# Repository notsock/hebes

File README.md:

# notcorne
Corne-styled Kailh Choc switch keyboard.

# Features
MCU: ATMega32u4 (Pro Micro)
Switches: Kailh Choc
Connectivity: RJ11 for both halves

# To-do
- Adjust collum stagger
- Adjust thumb cluster

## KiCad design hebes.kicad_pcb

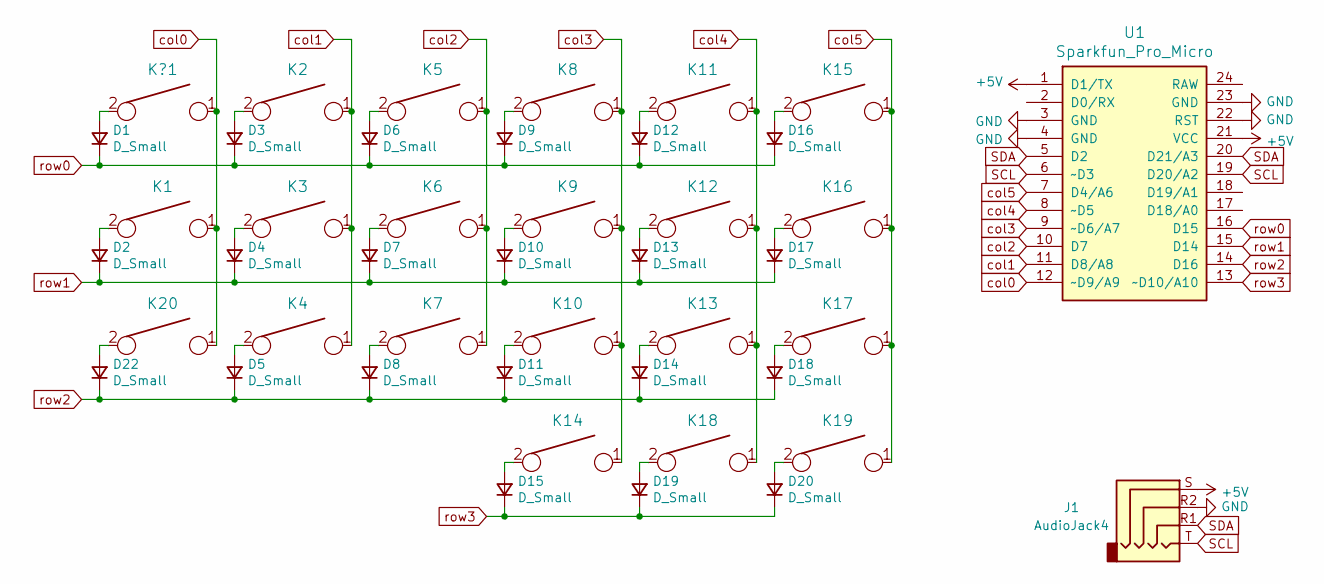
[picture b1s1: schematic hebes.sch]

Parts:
D1, D2, D3, D4, D5, D6, D7, D8, D9, D10, D11, D12, D13, D14, D15, D16, D17, D18, D19, D20, D22: D_Small; D_DO-34_SOD68_P2.54mm_Vertical_KathodeUp
J1: AudioJack4; Jack_3.5mm_PJ320D_Horizontal
K1, K2, K3, K4, K5, K6, K7, K8, K9, K10, K11, K12, K13, K14, K15, K16, K17, K18, K19, K20: KEYSW; SW_PG1350_reversible
K?1: KEYSW; SW_PG1350_reversible
U1: Sparkfun_Pro_Micro

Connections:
+5V: J1.S, U1.1 (D1/TX), U1.21 (VCC); also elsewhere on the board
GND: J1.R2, U1.3 (GND), U1.4 (GND), U1.22 (RST), U1.23 (GND); also elsewhere on the board
unnamed: D1.2 (A), K?1.2
unnamed: D2.2 (A), K1.2
unnamed: D3.2 (A), K2.2
unnamed: D4.2 (A), K3.2
unnamed: D5.2 (A), K4.2
unnamed: D6.2 (A), K5.2
unnamed: D7.2 (A), K6.2
unnamed: D8.2 (A), K7.2
unnamed: D9.2 (A), K8.2
unnamed: D10.2 (A), K9.2
unnamed: D11.2 (A), K10.2
unnamed: D12.2 (A), K11.2
unnamed: D13.2 (A), K12.2
unnamed: D14.2 (A), K13.2
unnamed: D15.2 (A), K14.2
unnamed: D16.2 (A), K15.2
unnamed: D17.2 (A), K16.2
unnamed: D18.2 (A), K17.2
unnamed: D19.2 (A), K18.2
unnamed: D20.2 (A), K19.2
unnamed: D22.2 (A), K20.2
SCL: J1.T, U1.6 (~~D3), U1.19 (D20/A2); also elsewhere on the board
SDA: J1.R1, U1.5 (D2), U1.20 (D21/A3); also elsewhere on the board
col0: K1.1, K20.1, K?1.1, U1.12 (~~D9/A9)
col1: K2.1, K3.1, K4.1, U1.11 (D8/A8)
col2: K5.1, K6.1, K7.1, U1.10 (D7)
col3: K8.1, K9.1, K10.1, K14.1, U1.9 (~~D6/A7)
col4: K11.1, K12.1, K13.1, K18.1, U1.8 (~~D5)
col5: K15.1, K16.1, K17.1, K19.1, U1.7 (D4/A6)
row0: D1.1 (K), D3.1 (K), D6.1 (K), D9.1 (K), D12.1 (K), D16.1 (K), U1.16 (D15)
row1: D2.1 (K), D4.1 (K), D7.1 (K), D10.1 (K), D13.1 (K), D17.1 (K), U1.15 (D14)
row2: D5.1 (K), D8.1 (K), D11.1 (K), D14.1 (K), D18.1 (K), D22.1 (K), U1.14 (D16)
row3: D15.1 (K), D19.1 (K), D20.1 (K), U1.13 (~~D10/A10)

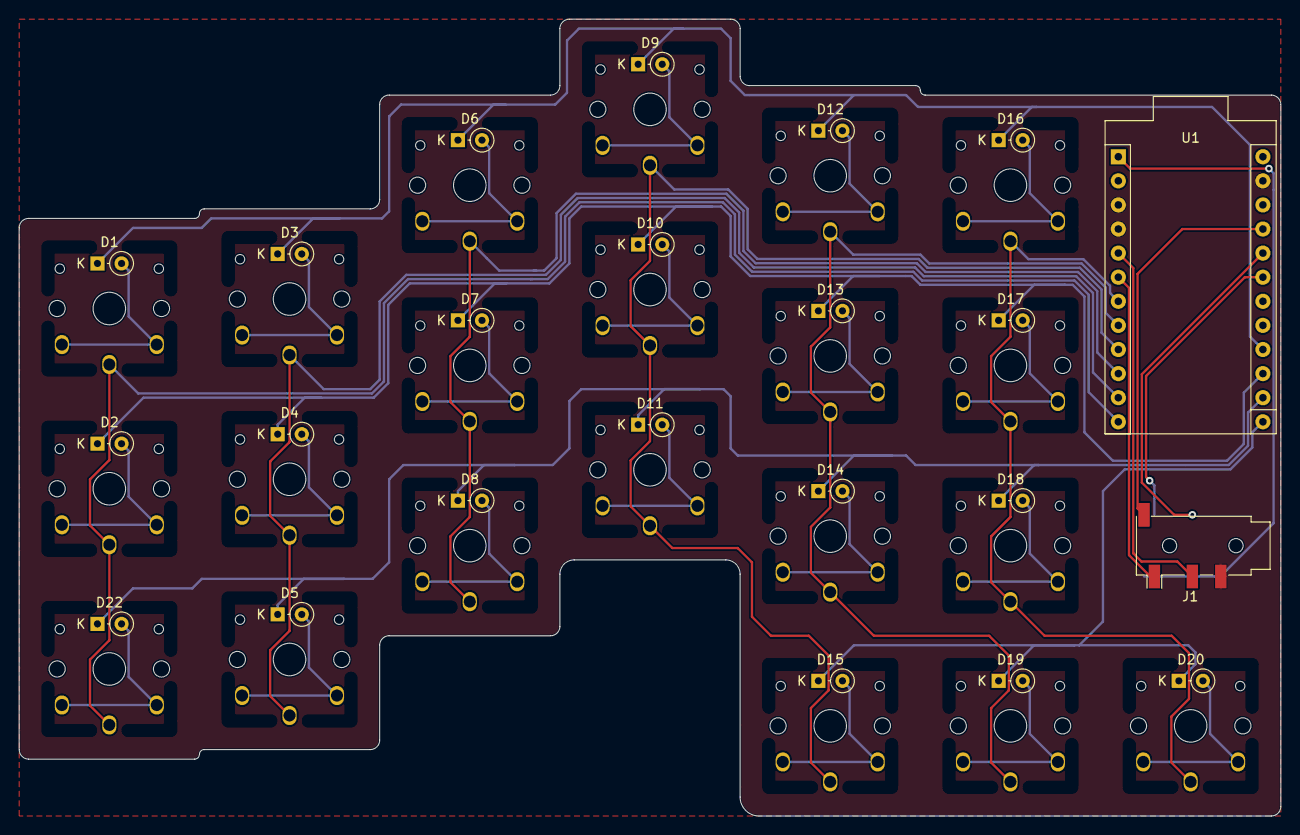
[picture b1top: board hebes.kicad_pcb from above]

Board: 2 copper layers, 133.0 x 84.0 mm, 45 parts (1 on the bottom side), 35 nets.

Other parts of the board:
J1#2: AudioJack4; Jack_3.5mm_PJ320D_Horizontal

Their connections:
+5V: J1#2.S; also elsewhere on the board
GND: J1#2.R2; also elsewhere on the board
SCL: J1#2.T; also elsewhere on the board
SDA: J1#2.R1; also elsewhere on the board

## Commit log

2021-04-21 rev 1
2021-07-21 new layout
